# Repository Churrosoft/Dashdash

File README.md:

# Dashdash
tablero de instrumentos por can para integrar con OpenEFI, cuando se nos ocurra algo mas original cambiamos el nombre

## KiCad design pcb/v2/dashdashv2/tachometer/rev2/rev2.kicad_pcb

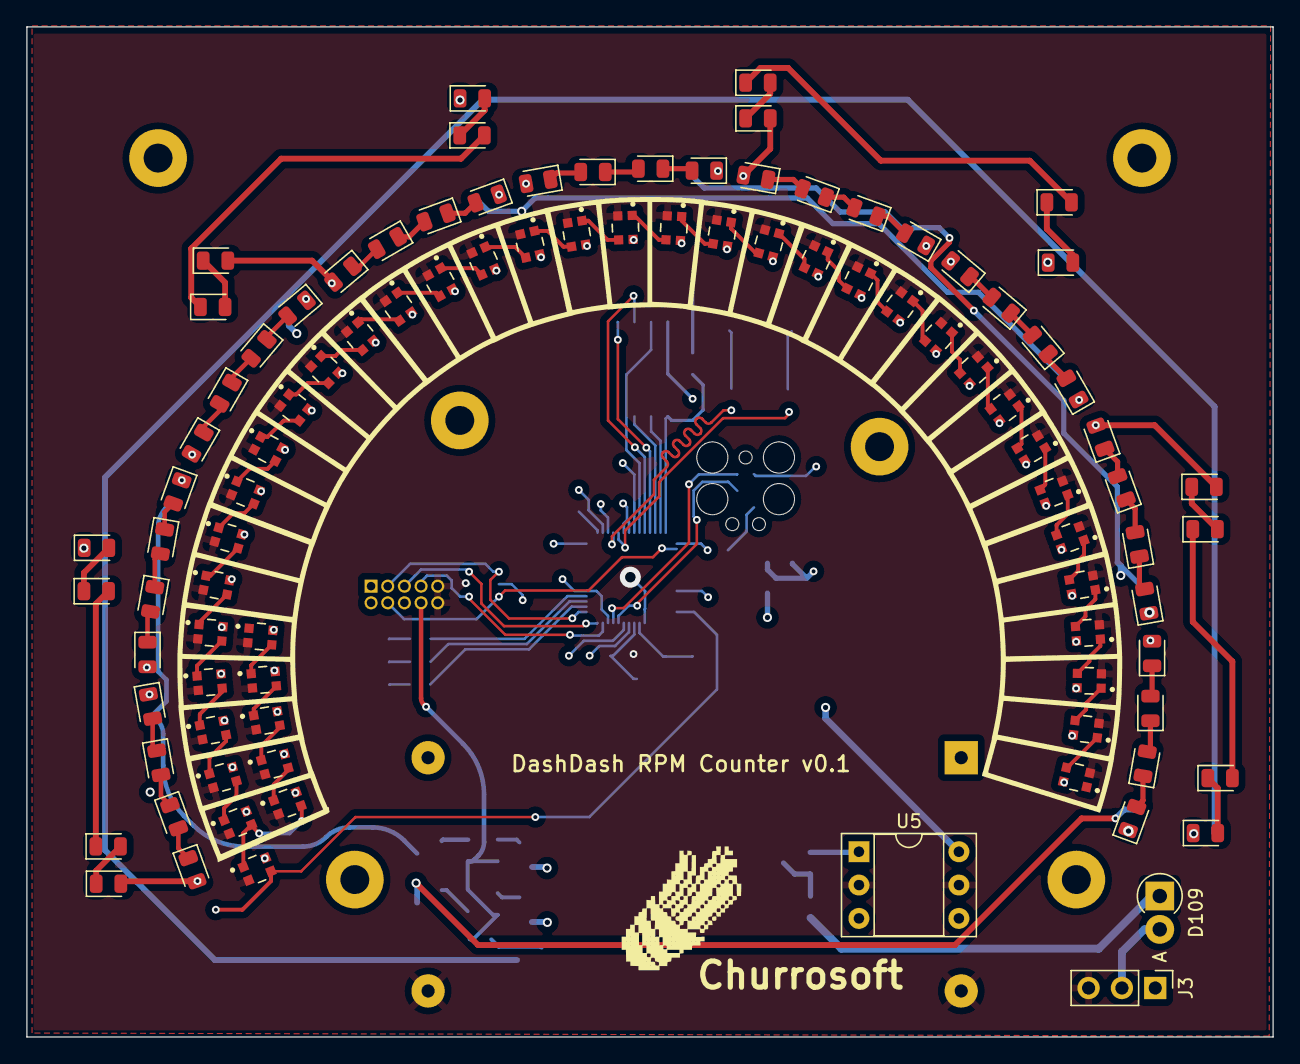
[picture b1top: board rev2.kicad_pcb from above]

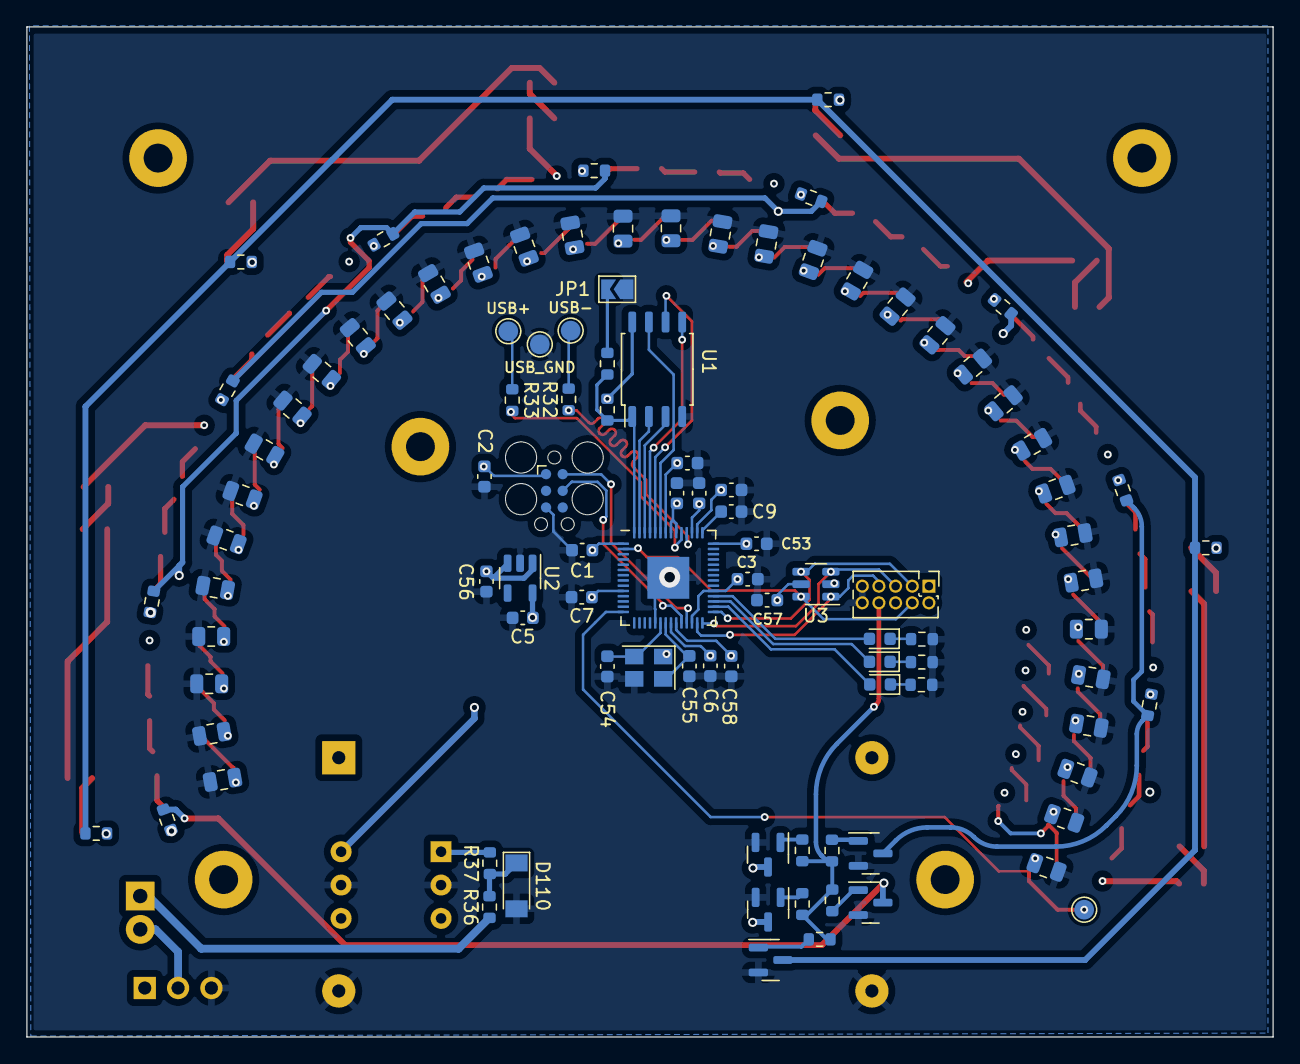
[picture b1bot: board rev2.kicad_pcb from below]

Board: 4 copper layers, 95.0 x 77.0 mm, 205 parts (102 on the bottom side), 138 nets.

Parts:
C1, C58: 2.2uF; C_0603_1608Metric
C2, C3, C4, C5, C6, C7, C8, C9, C10, C11, C53, C56: 100nF; C_0603_1608Metric
C12, C13, C14, C15, C16, C17, C18, C19, C20, C21, C22, C23, C24, C25, C26, C27, C28, C29, C30, C31, C32, C33, C34, C35, C36, C37, C38, C39, C40, C41, C42, C43, C44, C45, C46, C47: 100nF; C_0805_2012Metric
C54, C55, C57: 30pF; C_0603_1608Metric
Churrosoft: LOGO
D1, D2, D3, D4, D5, D6, D7, D8, D9, D10, D11, D12, D13, D14, D15, D16, D17, D18, D19, D20, D21, D22, D23, D24, D25, D26, D27, D28, D29, D30, D31, D32, D33, D34, D35, D36, D111, D112, D113, D114, D115: WS2812B; LED_WS2812-2020
D46, D47, D52, D53, D54, D55, D56, D57, D58, D59, D60, D61, D62, D63, D64, D65, D66, D67, D68, D69, D70, D71, D72, D73, D74, D75, D76, D77, D78, D79, D80, D81, D82, D83, D84, D85, D86, D87, D88, D89, D90, D91, D92, D93, D94, D95, D96, D97, D98, D99, D100, D101: LED; LED_0805_2012Metric
D106: GREEN; LED_0603_1608Metric
D107: BLUE; LED_0603_1608Metric
D108: RED; LED_0603_1608Metric
D109: 1N4007; D_DO-41_SOD81_P2.54mm_Vertical_AnodeUp
D110: BZV55B5V1; D_MiniMELF
H1, H2, H3, H6, H7, H8: MountingHole; MountingHole_2.2mm_M2_Pad
H4, H11: USB_GND; TestPoint_Pad_D1.5mm
H9: USB-; TestPoint_Pad_D1.5mm
H10: USB+; TestPoint_Pad_D1.5mm
J1: Tag connect; Tag-Connect_TC2030-IDC-FP_2x03_P1.27mm_Vertical
J2: RPM_CONN1; PinHeader_2x05_P1.27mm_Vertical
J3: Conn_01x03; PinHeader_1x03_P2.54mm_Vertical
JP1: BOOTSEL; SolderJumper-2_P1.3mm_Open_TrianglePad1.0x1.5mm
Q1, Q2, Q6, Q7, Q8: BSS138; SOT-23
R1, R2, R6, R7, R11, R12, R13, R14, R15, R18, R23, R24, R25, R26, R27, R28, R29, R30, R36: 1k 1/10W +-1%; R_0603_1608Metric
R21: 10k; R_0603_1608Metric
R22, R31, R34, R35: 1k; R_0603_1608Metric
R32, R33: 27R; R_0603_1608Metric
R37: 330R 1/10W +-1%; R_0603_1608Metric
U1: W25Q128JVS; SOIC-8_5.23x5.23mm_P1.27mm
U2: LP5907MFX-3.3; SOT-23-5
U3: SRV05-4; SOT-23-6
U4: RP2040; QFN-56-1EP_7x7mm_P0.4mm_EP3.2x3.2mm
U5: H11L1; DIP-6_W7.62mm_Socket
U6: YAAJ_DCDC_StepDown_LM2596
Y1: 12MHz; Crystal_SMD_3225-4Pin_3.2x2.5mm

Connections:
+1V1: C10.1, C11.1, C58.2, U4.23 (DVDD), U4.45 (VREG_VOUT), U4.50 (DVDD)
+3V3: C1.2, C2.1, C3.1, C4.1, C5.1, C6.1, C7.1, C8.1, C53.2, C57.2, J1.1, R21.2, U1.8 (VCC), U2.5 (OUT), U3.5 (VP), U4.1 (IOVDD), U4.10 (IOVDD), U4.22 (IOVDD), U4.26 (RUN), U4.33 (IOVDD), U4.42 (IOVDD), U4.44 (VREG_IN), U4.48 (USB_VDD), U4.49 (IOVDD), U5.6
+5VA: C12.2, C13.2, C14.2, C15.2, C16.2, C17.2, C18.2, C19.2, C20.2, C21.2, C22.2, C23.2, C24.2, C25.2, C26.2, C27.2, C28.2, C29.2, C30.2, C31.2, C32.2, C33.2, C34.2, C35.2, C36.2, C37.2, C38.2, C39.2, C40.2, C41.2, C42.2, C43.2, C44.2, C45.2, C46.2, C47.2, C56.1, D1.4 (VDD), D2.4 (VDD), D3.4 (VDD), D4.4 (VDD), D5.4 (VDD), D6.4 (VDD), D7.4 (VDD), D8.4 (VDD), D9.4 (VDD), D10.4 (VDD), D11.4 (VDD), D12.4 (VDD), D13.4 (VDD), D14.4 (VDD), D15.4 (VDD), D16.4 (VDD), D17.4 (VDD), D18.4 (VDD), D19.4 (VDD), D20.4 (VDD), D21.4 (VDD), D22.4 (VDD), D23.4 (VDD), D24.4 (VDD), D25.4 (VDD), D26.4 (VDD), D27.4 (VDD), D28.4 (VDD), D29.4 (VDD), D30.4 (VDD), D31.4 (VDD), D32.4 (VDD), D33.4 (VDD), D34.4 (VDD), D35.4 (VDD), D36.4 (VDD), D111.4 (VDD), D112.4 (VDD), D113.4 (VDD), D114.4 (VDD), D115.4 (VDD), U2.1 (IN), U2.3 (EN), U6.4 (Vout)
+12LF: D46.2 (A), D47.2 (A), D58.2 (A), D62.2 (A), D66.2 (A), D70.2 (A), D74.2 (A), D78.2 (A), D82.2 (A), D86.2 (A), D90.2 (A), D94.2 (A), D98.2 (A), J2.1, J2.2, J3.1, U6.1 (Vin)
/BA_1: Q1.3 (D), R27.2, R29.2
/BA_2: Q2.3 (D), R28.2, R30.2
/BA_3: Q7.3 (D), R23.2, R24.2
/BA_4: Q6.3 (D), R18.2, R25.2, R26.2
/BA_5: Q8.3 (D), R6.2, R12.2, R13.2, R15.2
/D+: R32.1, U4.46 (USB_DM)
/D-: R33.2, U4.47 (USB_DP)
/LED_BLUE: D107.2 (A), U4.31 (GPIO20)
/LED_GREEN: D106.2 (A), U4.30 (GPIO19)
/LED_RED: D108.2 (A), U4.32 (GPIO21)
/QSPI_SCLK: U1.6 (CLK), U4.52 (QSPI_SCLK)
/QSPI_SD0: U1.5 (DI(IO0)), U4.53 (QSPI_SD0)
/QSPI_SD1: U1.2 (DO(IO1)), U4.55 (QSPI_SD1)
/QSPI_SD2: U1.3 (IO2), U4.54 (QSPI_SD2)
/QSPI_SD3: U1.7 (IO3), U4.51 (QSPI_SD3)
/QSPI_SS: R21.1, R22.1, U1.1 (~CS), U4.56 (QSPI_SS)
/RPM_IN: D109.2 (A), J3.2
/SYS_SWCLK: J1.4, U4.24 (SWCLK)
/SYS_SWDIO: J1.2, U4.25 (SWD)
/TACH_DIN: D1.3 (DIN), H4.1, U4.14 (GPIO11)
/USB_D+: H10.1, R33.1
/USB_D-: H9.1, R32.2
/xin: C54.2, U4.20 (XIN), Y1.2
/xout: C55.2, U4.21 (XOUT), Y1.4
CLK: J2.3, U3.4 (IO3), U4.29 (GPIO18)
GND: C1.1, C2.2, C3.2, C4.2, C5.2, C6.2, C7.2, C8.2, C9.2, C10.2, C11.2, C12.1, C13.1, C14.1, C15.1, C16.1, C17.1, C18.1, C19.1, C20.1, C21.1, C22.1, C23.1, C24.1, C25.1, C26.1, C27.1, C28.1, C29.1, C30.1, C31.1, C32.1, C33.1, C34.1, C35.1, C36.1, C37.1, C38.1, C39.1, C40.1, C41.1, C42.1, C43.1, C44.1, C45.1, C46.1, C47.1, C53.1, C54.1, C55.1, C56.2, C57.1, C58.1, D1.2 (VSS), D2.2 (VSS), D3.2 (VSS), D4.2 (VSS), D5.2 (VSS), D6.2 (VSS), D7.2 (VSS), D8.2 (VSS), D9.2 (VSS), D10.2 (VSS), D11.2 (VSS), D12.2 (VSS), D13.2 (VSS), D14.2 (VSS), D15.2 (VSS), D16.2 (VSS), D17.2 (VSS), D18.2 (VSS), D19.2 (VSS), D20.2 (VSS), D21.2 (VSS), D22.2 (VSS), D23.2 (VSS), D24.2 (VSS), D25.2 (VSS), D26.2 (VSS), D27.2 (VSS), D28.2 (VSS), D29.2 (VSS), D30.2 (VSS), D31.2 (VSS), D32.2 (VSS), D33.2 (VSS), D34.2 (VSS), D35.2 (VSS), D36.2 (VSS), D110.2 (A), D111.2 (VSS), D112.2 (VSS), D113.2 (VSS), D114.2 (VSS), D115.2 (VSS), H11.1, J1.5, J2.9, J2.10, J3.3, JP1.1 (A), Q1.2 (S), Q2.2 (S), Q6.2 (S), Q7.2 (S), Q8.2 (S), R31.1, R34.1, R35.1, U1.4 (GND), U2.2 (GND), U3.2 (VN), U4.19 (TESTEN), U4.57 (GND), U5.2, U5.5, U6.2 (GND), U6.3 (GND), Y1.1, Y1.3
MISO: J2.5, U3.3 (IO2), U4.28 (GPIO17)
MOSI: J2.7, U3.1 (IO1), U4.27 (GPIO16)
unnamed: D1.1 (DOUT), D2.3 (DIN), D111.3 (DIN)
unnamed: D2.1 (DOUT), D3.3 (DIN)
unnamed: D3.1 (DOUT), D4.3 (DIN)
unnamed: D4.1 (DOUT), D5.3 (DIN)
unnamed: D5.1 (DOUT), D6.3 (DIN)
unnamed: D6.1 (DOUT), D7.3 (DIN)
unnamed: D7.1 (DOUT), D8.3 (DIN)
unnamed: D8.1 (DOUT), D9.3 (DIN)
unnamed: D10.1 (DOUT), D11.3 (DIN)
unnamed: D9.1 (DOUT), D10.3 (DIN)
unnamed: D11.1 (DOUT), D12.3 (DIN)
unnamed: D12.1 (DOUT), D13.3 (DIN)
unnamed: D13.1 (DOUT), D14.3 (DIN)
unnamed: D14.1 (DOUT), D15.3 (DIN)
unnamed: D15.1 (DOUT), D16.3 (DIN)
unnamed: D16.1 (DOUT), D17.3 (DIN)
unnamed: D17.1 (DOUT), D18.3 (DIN)
unnamed: D18.1 (DOUT), D19.3 (DIN)
unnamed: D19.1 (DOUT), D20.3 (DIN)
unnamed: D20.1 (DOUT), D21.3 (DIN)
unnamed: D21.1 (DOUT), D22.3 (DIN)
unnamed: D22.1 (DOUT), D23.3 (DIN)
unnamed: D23.1 (DOUT), D24.3 (DIN)
unnamed: D24.1 (DOUT), D25.3 (DIN)
unnamed: D25.1 (DOUT), D26.3 (DIN)
unnamed: D26.1 (DOUT), D27.3 (DIN)
unnamed: D27.1 (DOUT), D28.3 (DIN)
unnamed: D28.1 (DOUT), D29.3 (DIN)
unnamed: D29.1 (DOUT), D30.3 (DIN)
unnamed: D30.1 (DOUT), D31.3 (DIN)
unnamed: D31.1 (DOUT), D32.3 (DIN)
unnamed: D32.1 (DOUT), D33.3 (DIN)
unnamed: D33.1 (DOUT), D34.3 (DIN)
unnamed: D34.1 (DOUT), D35.3 (DIN)
unnamed: D35.1 (DOUT), D36.3 (DIN)
unnamed: D46.1 (K), D52.2 (A)
unnamed: D47.1 (K), D53.2 (A)
unnamed: D52.1 (K), D54.2 (A)
unnamed: D53.1 (K), D55.2 (A)
unnamed: D54.1 (K), D56.2 (A)
unnamed: D55.1 (K), D57.2 (A)
unnamed: D56.1 (K), R29.1
unnamed: D57.1 (K), R30.1
unnamed: D58.1 (K), D59.2 (A)
unnamed: D59.1 (K), D60.2 (A)
unnamed: D60.1 (K), D61.2 (A)
unnamed: D61.1 (K), R27.1
unnamed: D62.1 (K), D63.2 (A)
unnamed: D63.1 (K), D64.2 (A)
unnamed: D64.1 (K), D65.2 (A)
unnamed: D65.1 (K), R28.1
unnamed: D66.1 (K), D67.2 (A)
unnamed: D67.1 (K), D68.2 (A)
unnamed: D68.1 (K), D69.2 (A)
unnamed: D69.1 (K), R23.1
unnamed: D70.1 (K), D71.2 (A)
unnamed: D71.1 (K), D72.2 (A)
unnamed: D72.1 (K), D73.2 (A)
unnamed: D73.1 (K), R24.1
unnamed: D74.1 (K), D75.2 (A)
unnamed: D75.1 (K), D76.2 (A)
unnamed: D76.1 (K), D77.2 (A)
unnamed: D77.1 (K), R25.1
unnamed: D78.1 (K), D79.2 (A)
unnamed: D79.1 (K), D80.2 (A)
unnamed: D80.1 (K), D81.2 (A)
unnamed: D81.1 (K), R26.1
unnamed: D82.1 (K), D83.2 (A)
unnamed: D83.1 (K), D84.2 (A)
unnamed: D84.1 (K), D85.2 (A)
unnamed: D85.1 (K), R6.1
unnamed: D86.1 (K), D87.2 (A)
unnamed: D87.1 (K), D88.2 (A)
unnamed: D88.1 (K), D89.2 (A)
unnamed: D89.1 (K), R12.1
unnamed: D90.1 (K), D91.2 (A)
unnamed: D91.1 (K), D92.2 (A)
unnamed: D92.1 (K), D93.2 (A)
unnamed: D93.1 (K), R13.1
unnamed: D94.1 (K), D95.2 (A)
unnamed: D95.1 (K), D96.2 (A)
unnamed: D96.1 (K), D97.2 (A)
unnamed: D97.1 (K), R18.1
unnamed: D98.1 (K), D99.2 (A)
unnamed: D100.1 (K), D101.2 (A)
unnamed: D99.1 (K), D100.2 (A)
unnamed: D101.1 (K), R15.1
unnamed: D106.1 (K), R31.2
unnamed: D107.1 (K), R34.2
unnamed: D108.1 (K), R35.2
unnamed: D109.1 (K), R36.1
unnamed: D110.1 (K), R36.2, R37.1
unnamed: D111.1 (DOUT), D112.3 (DIN)
unnamed: D112.1 (DOUT), D113.3 (DIN)
unnamed: D113.1 (DOUT), D114.3 (DIN)
unnamed: D114.1 (DOUT), D115.3 (DIN)
unnamed: JP1.2 (B), R22.2
unnamed: Q1.1 (G), R1.1
unnamed: Q2.1 (G), R7.1
unnamed: Q6.1 (G), R11.1
unnamed: Q7.1 (G), R14.1
unnamed: Q8.1 (G), R2.1
unnamed: R37.2, U5.1
PWM_BACK_RPM: J2.8, R1.2, R2.2, R7.2, R11.2, R14.2
RPM_CS: J2.4, U3.6 (IO4), U4.2 (GPIO0)
VDDA: C9.1, U4.43 (ADC_AVDD)

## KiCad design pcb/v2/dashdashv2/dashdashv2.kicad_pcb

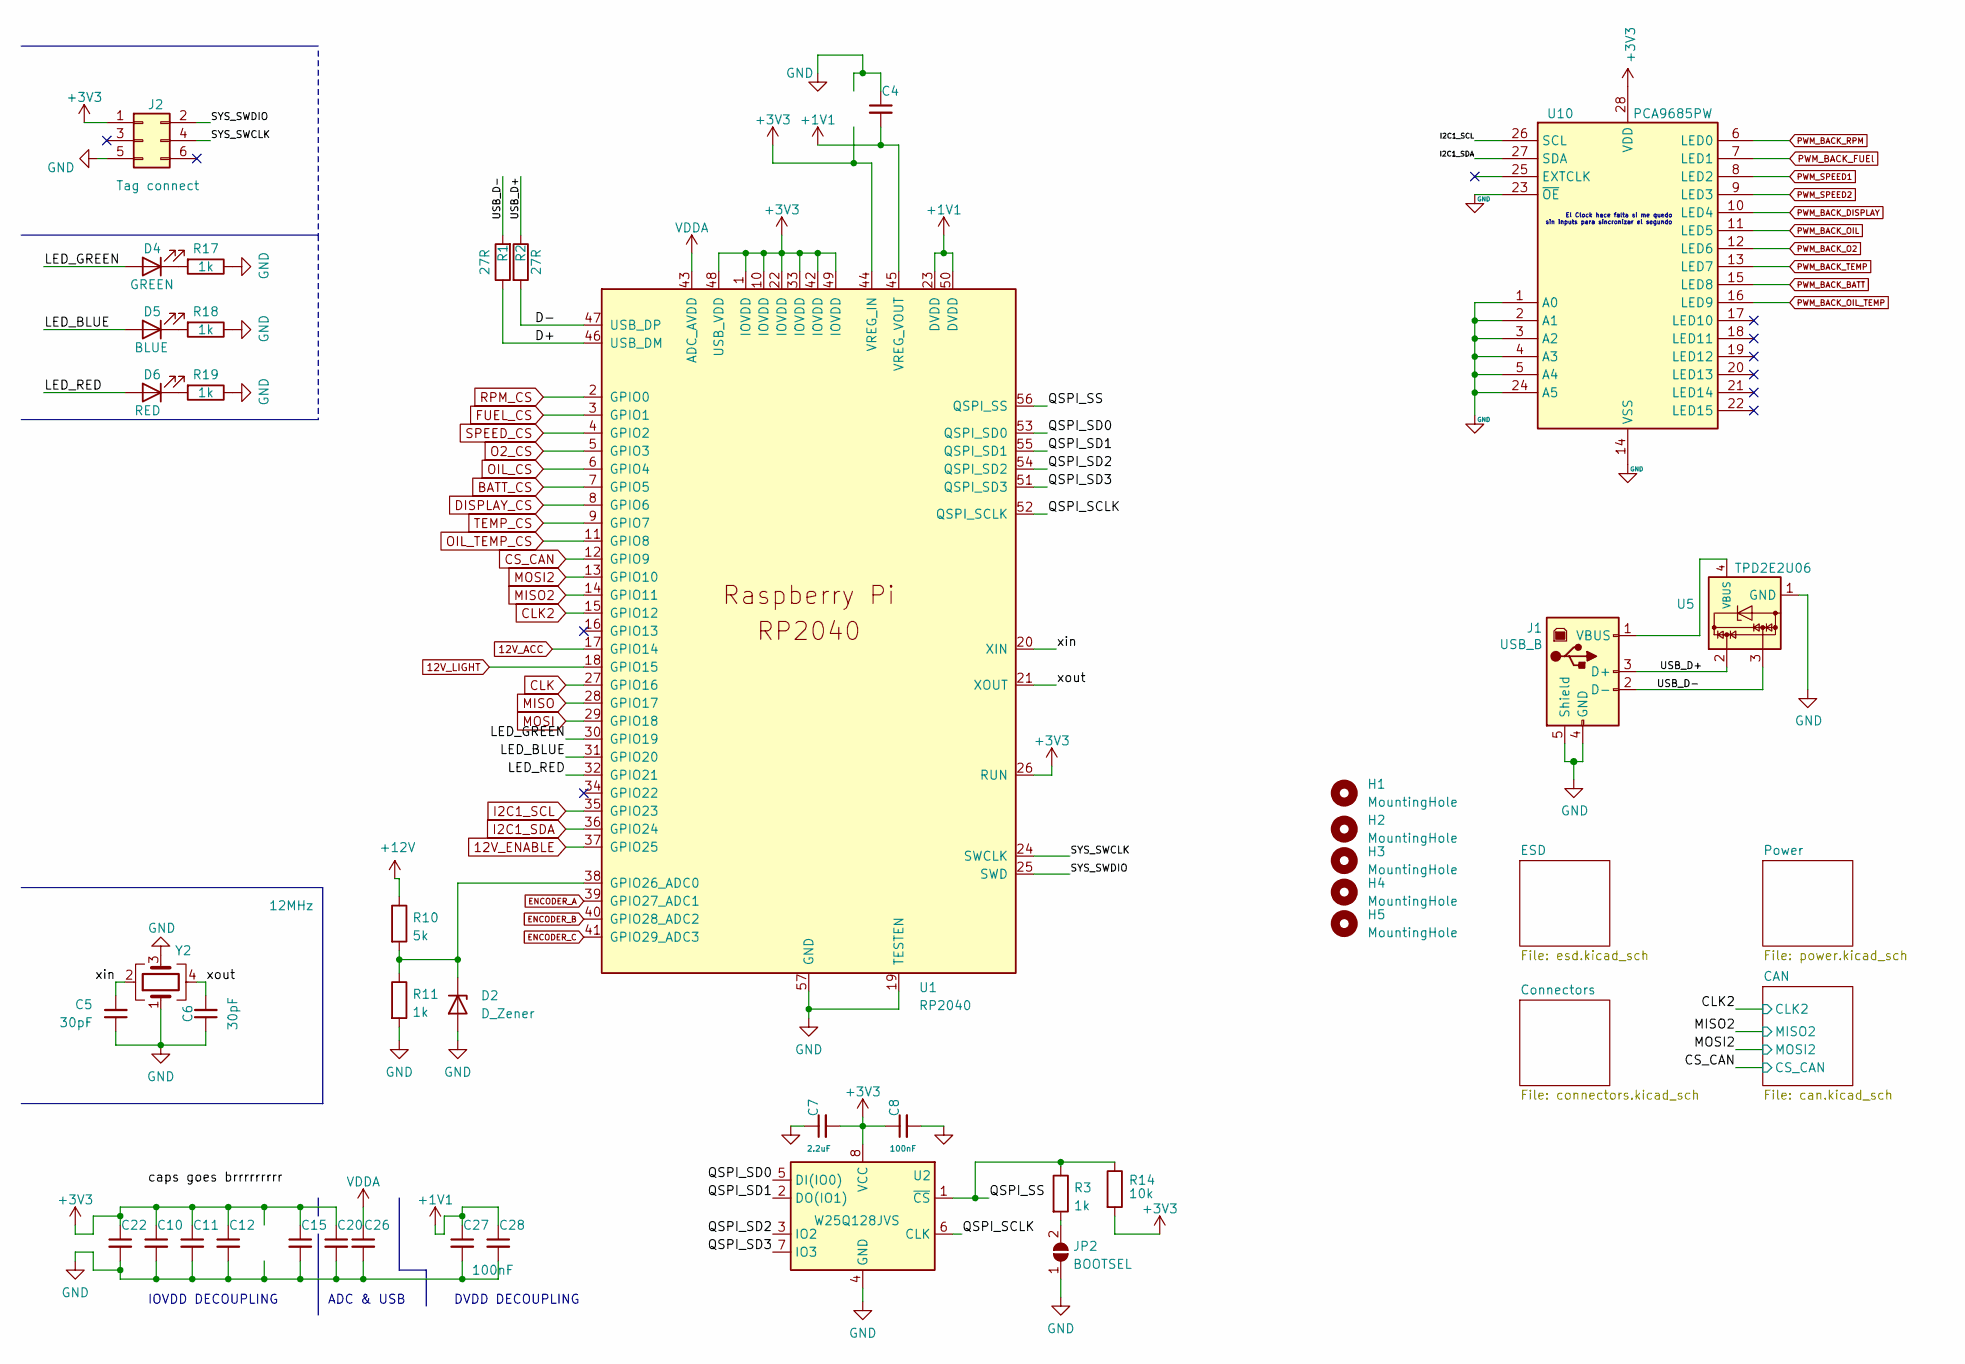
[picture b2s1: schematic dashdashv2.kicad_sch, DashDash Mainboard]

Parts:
C4, C7: 2.2uF; C_0603_1608Metric
C5, C6: 30pF; C_0603_1608Metric
C8, C10, C11, C12, C15, C20, C22, C26, C27, C28: 100nF; C_0603_1608Metric
D2: D_Zener; D_SOD-123F
D4: GREEN; LED_0603_1608Metric; LCSC C72043
D5: BLUE; LED_0603_1608Metric; LCSC C72041
D6: RED; LED_0603_1608Metric; LCSC C72041
H1, H2, H3, H4, H5: MountingHole; MountingHole_2.2mm_M2_Pad_Via
J1: USB_B; USB_B_OST_USB-B1HSxx_Horizontal
J2: Tag connect; Tag-Connect_TC2030-IDC-FP_2x03_P1.27mm_Vertical
JP2: BOOTSEL; SolderJumper-2_P1.3mm_Open_TrianglePad1.0x1.5mm
R1, R2: 27R; R_0603_1608Metric
R3, R11, R17, R18, R19: 1k; R_0603_1608Metric
R10: 5k; R_0603_1608Metric
R14: 10k; R_0603_1608Metric
U1: RP2040; QFN-56-1EP_7x7mm_P0.4mm_EP3.2x3.2mm
U2: W25Q128JVS; SOIC-8_5.23x5.23mm_P1.27mm
U5: TPD2E2U06; SOT-143; LCSC C2987149
U10: PCA9685PW; TSSOP-28_4.4x9.7mm_P0.65mm
Y2: 12MHz; Crystal_SMD_3225-4Pin_3.2x2.5mm; LCSC C9002

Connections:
12V_ACC: U1.17 (GPIO14); also elsewhere on the board
12V_ENABLE: U1.37 (GPIO25); also elsewhere on the board
12V_LIGHT: U1.18 (GPIO15); also elsewhere on the board
+1V1: C4.2, C27.1, C28.1, U1.23 (DVDD), U1.45 (VREG_VOUT), U1.50 (DVDD)
+3V3: C7.2, C8.1, C10.1, C11.1, C12.1, C15.1, C20.1, C22.1, J2.1, R14.2, U1.1 (IOVDD), U1.10 (IOVDD), U1.22 (IOVDD), U1.26 (RUN), U1.33 (IOVDD), U1.42 (IOVDD), U1.44 (VREG_IN), U1.48 (USB_VDD), U1.49 (IOVDD), U2.8 (VCC), U10.28 (VDD); also elsewhere on the board
+12V: R10.1; also elsewhere on the board
/D+: R1.1, U1.46 (USB_DM)
/D-: R2.2, U1.47 (USB_DP)
/LED_BLUE: D5.2 (A), U1.31 (GPIO20)
/LED_GREEN: D4.2 (A), U1.30 (GPIO19)
/LED_RED: D6.2 (A), U1.32 (GPIO21)
/QSPI_SCLK: U1.52 (QSPI_SCLK), U2.6 (CLK)
/QSPI_SD0: U1.53 (QSPI_SD0), U2.5 (DI(IO0))
/QSPI_SD1: U1.55 (QSPI_SD1), U2.2 (DO(IO1))
/QSPI_SD2: U1.54 (QSPI_SD2), U2.3 (IO2)
/QSPI_SD3: U1.51 (QSPI_SD3), U2.7 (IO3)
/QSPI_SS: R3.1, R14.1, U1.56 (QSPI_SS), U2.1 (~CS)
/SYS_SWCLK: J2.4, U1.24 (SWCLK)
/SYS_SWDIO: J2.2, U1.25 (SWD)
/USB_D+: J1.3 (D+), R2.1, U5.2
/USB_D-: J1.2 (D-), R1.2, U5.3
/xin: C5.2, U1.20 (XIN), Y2.2
/xout: C6.2, U1.21 (XOUT), Y2.4
BATT_CS: U1.7 (GPIO5); also elsewhere on the board
CLK: U1.27 (GPIO16); also elsewhere on the board
CLK2: U1.15 (GPIO12); also elsewhere on the board
CS_CAN: U1.12 (GPIO9); also elsewhere on the board
DISPLAY_CS: U1.8 (GPIO6); also elsewhere on the board
ENCODER_A: U1.39 (GPIO27_ADC1); also elsewhere on the board
ENCODER_B: U1.40 (GPIO28_ADC2); also elsewhere on the board
ENCODER_C: U1.41 (GPIO29_ADC3); also elsewhere on the board
FUEL_CS: U1.3 (GPIO1); also elsewhere on the board
GND: C4.1, C5.1, C6.1, C7.1, C8.2, C10.2, C11.2, C12.2, C15.2, C20.2, C22.2, C26.2, C27.2, C28.2, D2.2 (A), J1.4 (GND), J1.5 (Shield), J2.5, JP2.1 (A), R11.2, R17.1, R18.1, R19.1, U1.19 (TESTEN), U1.57 (GND), U2.4 (GND), U5.1 (GND), U10.1 (A0), U10.2 (A1), U10.3 (A2), U10.4 (A3), U10.5 (A4), U10.14 (VSS), U10.23 (~OE), U10.24 (A5), Y2.1, Y2.3; also elsewhere on the board
I2C1_SCL: U1.35 (GPIO23), U10.26 (SCL)
I2C1_SDA: U1.36 (GPIO24), U10.27 (SDA)
MISO: U1.28 (GPIO17); also elsewhere on the board
MISO2: U1.14 (GPIO11); also elsewhere on the board
MOSI: U1.29 (GPIO18); also elsewhere on the board
MOSI2: U1.13 (GPIO10); also elsewhere on the board
unnamed: D2.1 (K), R10.2, R11.1, U1.38 (GPIO26_ADC0)
unnamed: D4.1 (K), R17.2
unnamed: D5.1 (K), R18.2
unnamed: D6.1 (K), R19.2
unnamed: J1.1 (VBUS), U5.4 (VBUS)
unnamed: JP2.2 (B), R3.2
O2_CS: U1.5 (GPIO3); also elsewhere on the board
OIL_CS: U1.6 (GPIO4); also elsewhere on the board
OIL_TEMP_CS: U1.11 (GPIO8); also elsewhere on the board
PWM_BACK_BATT: U10.15 (LED8); also elsewhere on the board
PWM_BACK_DISPLAY: U10.10 (LED4); also elsewhere on the board
PWM_BACK_FUEl: U10.7 (LED1); also elsewhere on the board
PWM_BACK_O2: U10.12 (LED6); also elsewhere on the board
PWM_BACK_OIL: U10.11 (LED5); also elsewhere on the board
PWM_BACK_OIL_TEMP: U10.16 (LED9); also elsewhere on the board
PWM_BACK_RPM: U10.6 (LED0); also elsewhere on the board
PWM_BACK_TEMP: U10.13 (LED7); also elsewhere on the board
PWM_SPEED1: U10.8 (LED2); also elsewhere on the board
PWM_SPEED2: U10.9 (LED3); also elsewhere on the board
RPM_CS: U1.2 (GPIO0); also elsewhere on the board
SPEED_CS: U1.4 (GPIO2); also elsewhere on the board
TEMP_CS: U1.9 (GPIO7); also elsewhere on the board
VDDA: C26.1, U1.43 (ADC_AVDD)

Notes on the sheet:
DVDD DECOUPLING
ADC & USB
IOVDD DECOUPLING
El Clock hace falta si me quedo sin inputs para sincronizar el segundo

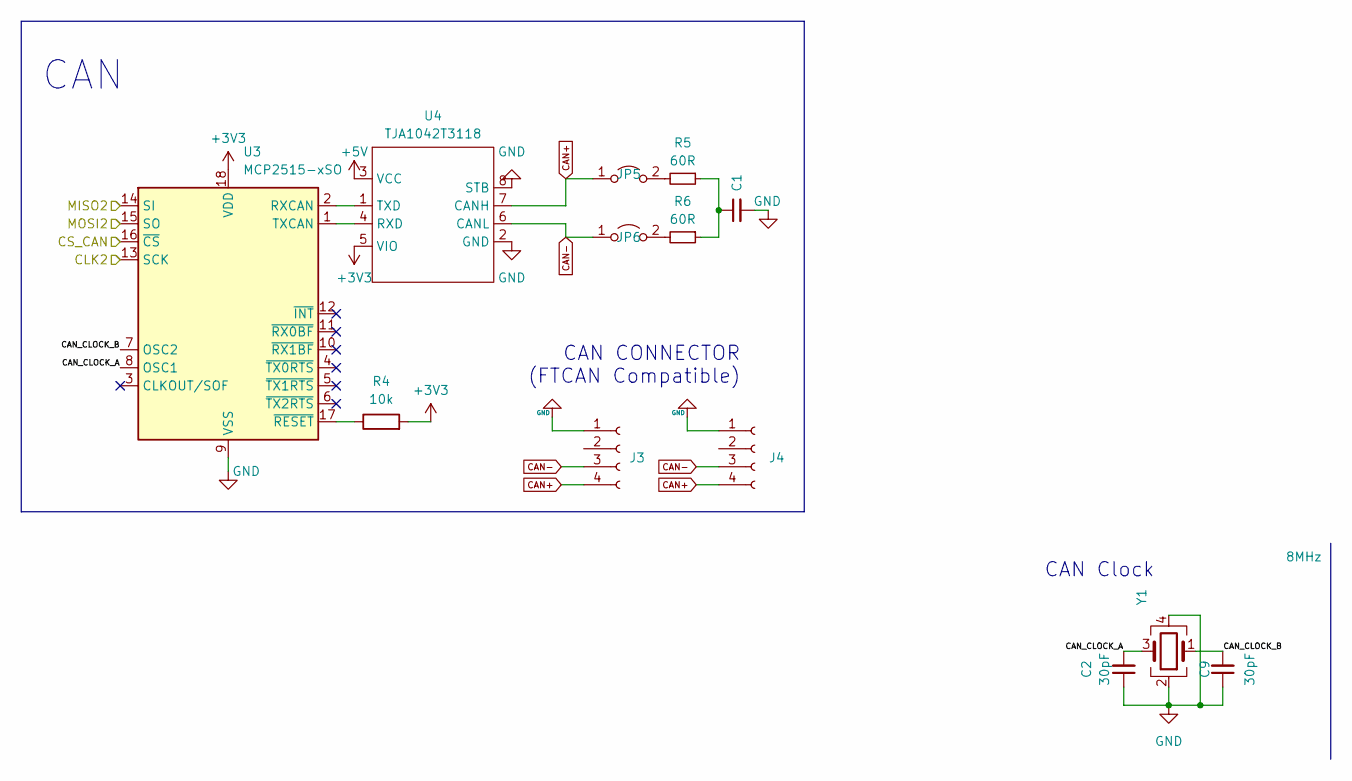
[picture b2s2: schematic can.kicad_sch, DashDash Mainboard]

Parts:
C1: 4.7nF; C_0805_2012Metric; LCSC C77475
C2, C9: 30pF; C_0603_1608Metric
J3, J4: Conn_01x04_Female; Molex_Mini-Fit_Jr_5569-04A1_2x02_P4.20mm_Horizontal
JP5, JP6: Jumper_2_Open; SolderJumper-2_P1.3mm_Open_RoundedPad1.0x1.5mm
R4: 10k; R_0603_1608Metric
R5, R6: 60R; R_1206_3216Metric
U3: MCP2515-xSO; SOIC-18W_7.5x11.6mm_P1.27mm
U4: TJA1042T3118; HTSOP-8-1EP_3.9x4.9mm_P1.27mm_EP2.4x3.2mm
Y1: 8MHz; Crystal_SMD_3225-4Pin_3.2x2.5mm; LCSC C9002

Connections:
+3V3: R4.2, U3.18 (VDD), U4.5 (VIO); also elsewhere on the board
+5V: U4.3 (VCC); also elsewhere on the board
/CAN/CAN_CLOCK_A: C2.2, U3.8 (OSC1), Y1.3
/CAN/CAN_CLOCK_B: C9.2, U3.7 (OSC2), Y1.1
CAN+: J3.4, J4.4, JP5.1 (A), U4.7 (CANH)
CAN-: J3.3, J4.3, JP6.1 (A), U4.6 (CANL)
CLK2: U3.13 (SCK); also elsewhere on the board
CS_CAN: U3.16 (~CS); also elsewhere on the board
GND: C1.2, C2.1, C9.1, J3.1, J4.1, U3.9 (VSS), U4.2 (GND), U4.8 (STB), Y1.2, Y1.4; also elsewhere on the board
MISO2: U3.14 (SI); also elsewhere on the board
MOSI2: U3.15 (SO); also elsewhere on the board
unnamed: C1.1, R5.1, R6.1
unnamed: JP5.2 (B), R5.2
unnamed: JP6.2 (B), R6.2
unnamed: R4.1, U3.17 (~RESET)
unnamed: U3.1 (TXCAN), U4.4 (RXD)
unnamed: U3.2 (RXCAN), U4.1 (TXD)

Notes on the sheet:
CAN
CAN Clock
CAN CONNECTOR (FTCAN Compatible)

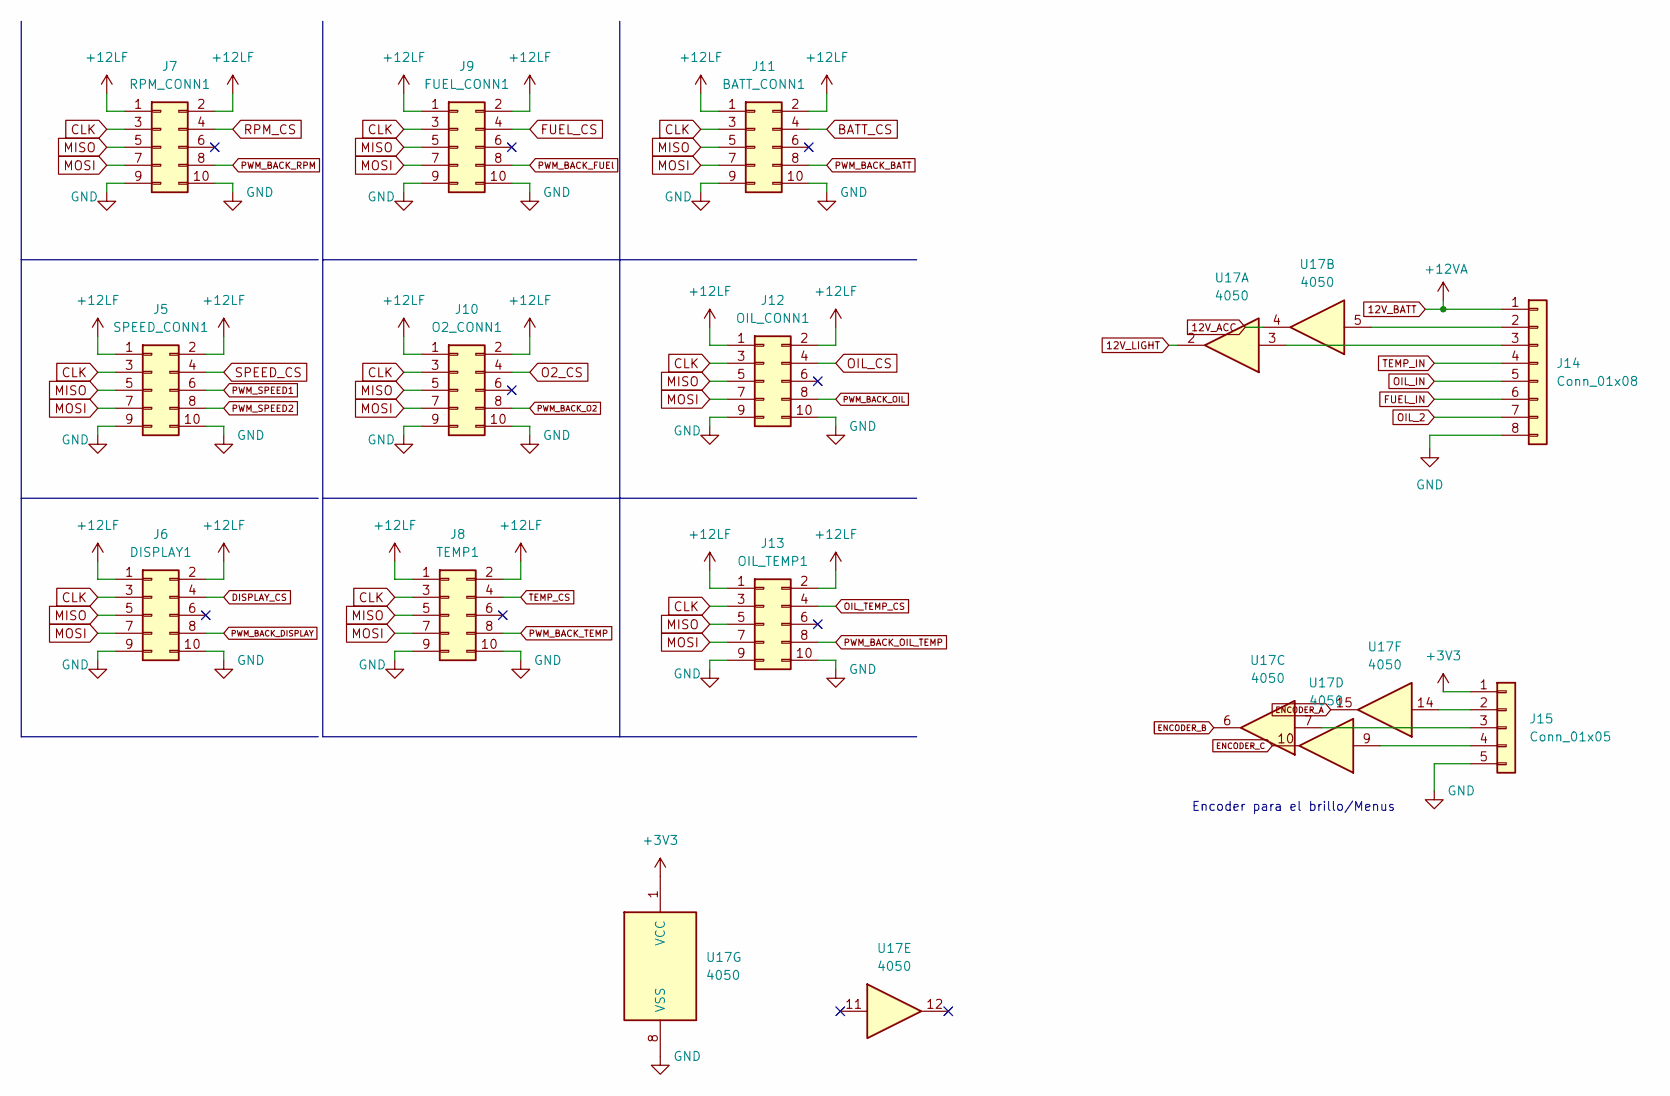
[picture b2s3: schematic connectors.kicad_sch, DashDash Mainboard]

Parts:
J5: SPEED_CONN1; PinHeader_2x05_P1.27mm_Vertical
J6: DISPLAY1; PinHeader_2x05_P1.27mm_Vertical
J7: RPM_CONN1; PinHeader_2x05_P1.27mm_Vertical
J8: TEMP1; PinHeader_2x05_P1.27mm_Vertical
J9: FUEL_CONN1; PinHeader_2x05_P1.27mm_Vertical
J10: O2_CONN1; PinHeader_2x05_P1.27mm_Vertical
J11: BATT_CONN1; PinHeader_2x05_P1.27mm_Vertical
J12: OIL_CONN1; PinHeader_2x05_P1.27mm_Vertical
J13: OIL_TEMP1; PinHeader_2x05_P1.27mm_Vertical
J14: Conn_01x08; Molex_Micro-Fit_3.0_43045-0800_2x04_P3.00mm_Horizontal
J15: Conn_01x05; PinHeader_1x05_P2.54mm_Vertical
U17: 4050; TSSOP-16_4.4x5mm_P0.65mm

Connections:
12V_ACC: U17.4; also elsewhere on the board
12V_BATT: J14.1; also elsewhere on the board
12V_LIGHT: U17.2; also elsewhere on the board
+3V3: J15.1, U17.1 (VCC); also elsewhere on the board
+12LF: J5.1, J5.2, J6.1, J6.2, J7.1, J7.2, J8.1, J8.2, J9.1, J9.2, J10.1, J10.2, J11.1, J11.2, J12.1, J12.2, J13.1, J13.2; also elsewhere on the board
BATT_CS: J11.4; also elsewhere on the board
CLK: J5.3, J6.3, J7.3, J8.3, J9.3, J10.3, J11.3, J12.3, J13.3; also elsewhere on the board
DISPLAY_CS: J6.4; also elsewhere on the board
ENCODER_A: U17.15; also elsewhere on the board
ENCODER_B: U17.6; also elsewhere on the board
ENCODER_C: U17.10; also elsewhere on the board
FUEL_CS: J9.4; also elsewhere on the board
FUEL_IN: J14.6
GND: J5.9, J5.10, J6.9, J6.10, J7.9, J7.10, J8.9, J8.10, J9.9, J9.10, J10.9, J10.10, J11.9, J11.10, J12.9, J12.10, J13.9, J13.10, J14.8, J15.5, U17.8 (VSS); also elsewhere on the board
MISO: J5.5, J6.5, J7.5, J8.5, J9.5, J10.5, J11.5, J12.5, J13.5; also elsewhere on the board
MOSI: J5.7, J6.7, J7.7, J8.7, J9.7, J10.7, J11.7, J12.7, J13.7; also elsewhere on the board
unnamed: J14.2, U17.5
unnamed: J14.3, U17.3
unnamed: J15.2, U17.14
unnamed: J15.3, U17.7
unnamed: J15.4, U17.9
O2_CS: J10.4; also elsewhere on the board
OIL_2: J14.7
OIL_CS: J12.4; also elsewhere on the board
OIL_IN: J14.5
OIL_TEMP_CS: J13.4; also elsewhere on the board
PWM_BACK_BATT: J11.8; also elsewhere on the board
PWM_BACK_DISPLAY: J6.8; also elsewhere on the board
PWM_BACK_FUEl: J9.8; also elsewhere on the board
PWM_BACK_O2: J10.8; also elsewhere on the board
PWM_BACK_OIL: J12.8; also elsewhere on the board
PWM_BACK_OIL_TEMP: J13.8; also elsewhere on the board
PWM_BACK_RPM: J7.8; also elsewhere on the board
PWM_BACK_TEMP: J8.8; also elsewhere on the board
PWM_SPEED1: J5.6; also elsewhere on the board
PWM_SPEED2: J5.8; also elsewhere on the board
RPM_CS: J7.4; also elsewhere on the board
SPEED_CS: J5.4; also elsewhere on the board
TEMP_CS: J8.4; also elsewhere on the board
TEMP_IN: J14.4

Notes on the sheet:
Encoder para el brillo/Menus

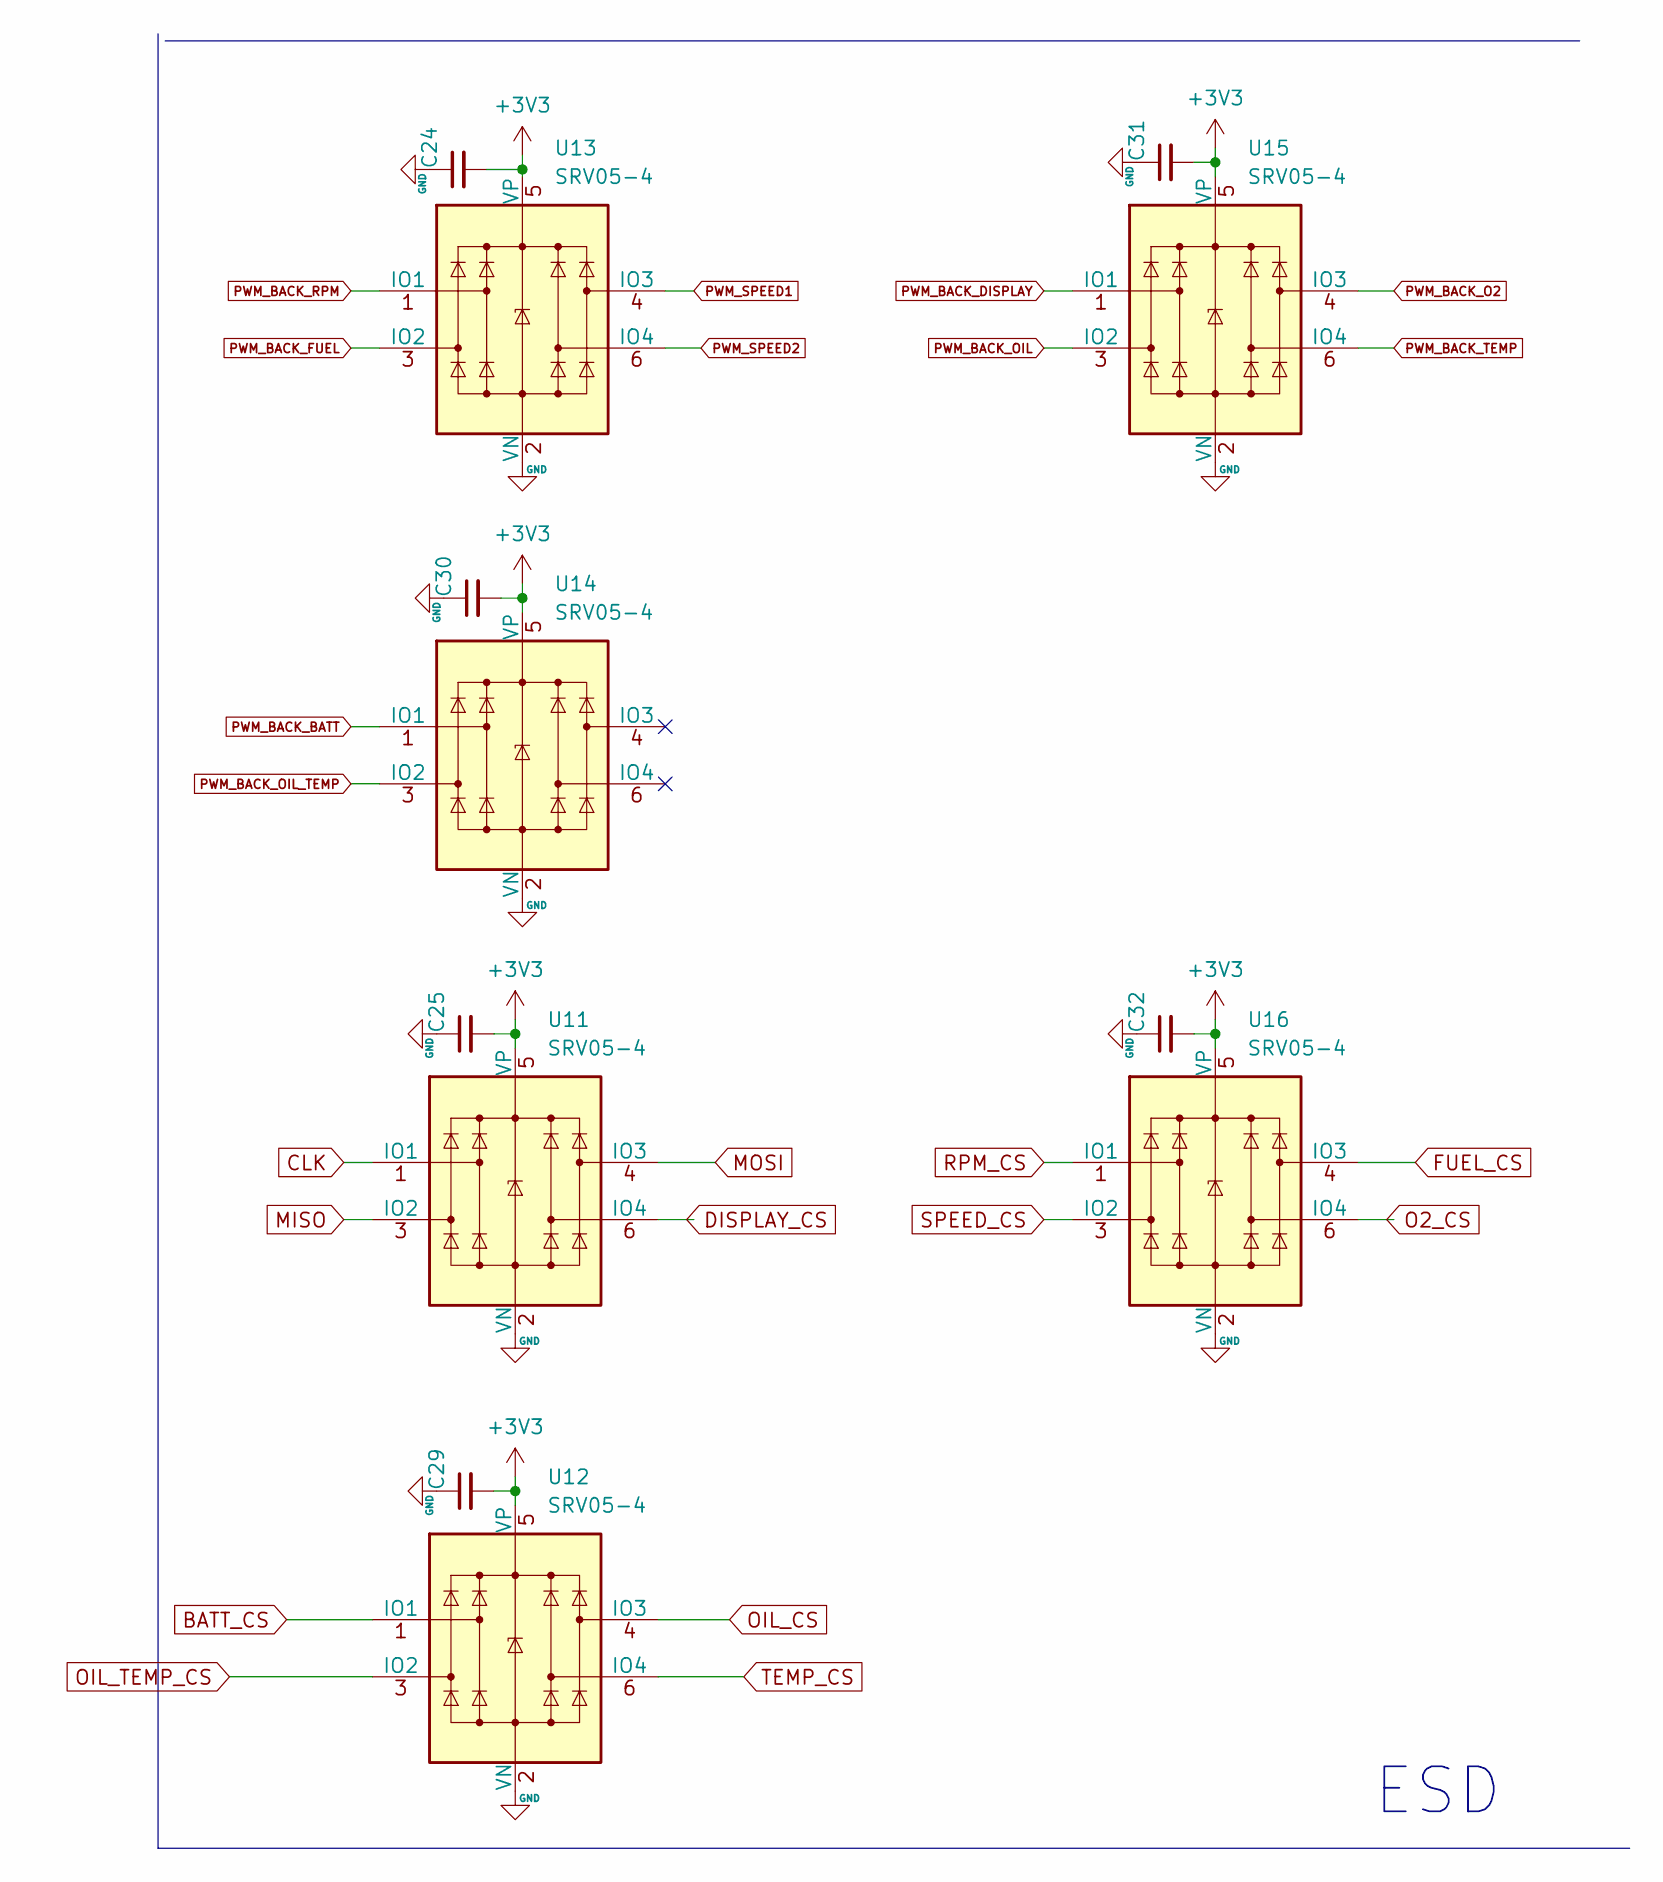
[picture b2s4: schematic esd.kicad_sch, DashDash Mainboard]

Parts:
C24, C25, C29, C30, C31, C32: 100nF; C_0603_1608Metric
U11, U12, U13, U14, U15, U16: SRV05-4; SOT-23-6

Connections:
+3V3: C24.2, C25.2, C29.2, C30.2, C31.2, C32.2, U11.5 (VP), U12.5 (VP), U13.5 (VP), U14.5 (VP), U15.5 (VP), U16.5 (VP); also elsewhere on the board
BATT_CS: U12.1 (IO1); also elsewhere on the board
CLK: U11.1 (IO1); also elsewhere on the board
DISPLAY_CS: U11.6 (IO4); also elsewhere on the board
FUEL_CS: U16.4 (IO3); also elsewhere on the board
GND: C24.1, C25.1, C29.1, C30.1, C31.1, C32.1, U11.2 (VN), U12.2 (VN), U13.2 (VN), U14.2 (VN), U15.2 (VN), U16.2 (VN); also elsewhere on the board
MISO: U11.3 (IO2); also elsewhere on the board
MOSI: U11.4 (IO3); also elsewhere on the board
O2_CS: U16.6 (IO4); also elsewhere on the board
OIL_CS: U12.4 (IO3); also elsewhere on the board
OIL_TEMP_CS: U12.3 (IO2); also elsewhere on the board
PWM_BACK_BATT: U14.1 (IO1); also elsewhere on the board
PWM_BACK_DISPLAY: U15.1 (IO1); also elsewhere on the board
PWM_BACK_FUEL: U13.3 (IO2)
PWM_BACK_O2: U15.4 (IO3); also elsewhere on the board
PWM_BACK_OIL: U15.3 (IO2); also elsewhere on the board
PWM_BACK_OIL_TEMP: U14.3 (IO2); also elsewhere on the board
PWM_BACK_RPM: U13.1 (IO1); also elsewhere on the board
PWM_BACK_TEMP: U15.6 (IO4); also elsewhere on the board
PWM_SPEED1: U13.4 (IO3); also elsewhere on the board
PWM_SPEED2: U13.6 (IO4); also elsewhere on the board
RPM_CS: U16.1 (IO1); also elsewhere on the board
SPEED_CS: U16.3 (IO2); also elsewhere on the board
TEMP_CS: U12.6 (IO4); also elsewhere on the board

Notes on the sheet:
ESD
